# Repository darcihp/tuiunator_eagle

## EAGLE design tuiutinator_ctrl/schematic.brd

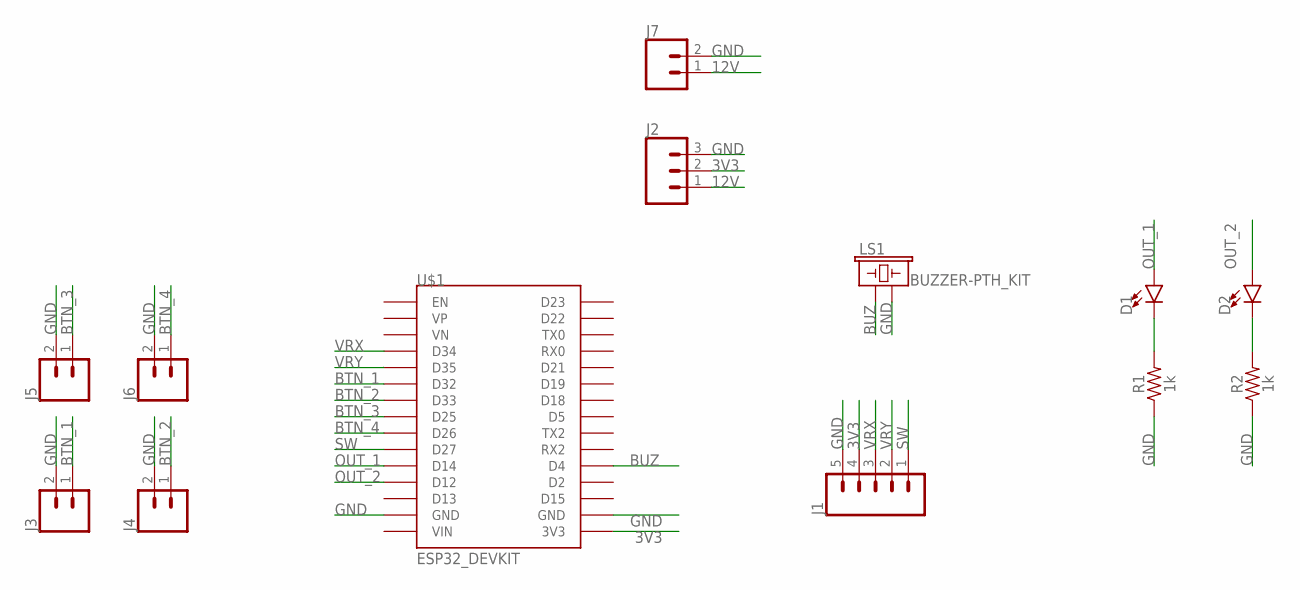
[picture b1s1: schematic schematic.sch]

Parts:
D1, D2: LED5MM; LED_5MM
J1: CONN_05LOCK; 1X05_LOCK
J2: CONN_03SCREW; SCREWTERMINAL-3.5MM-3
J3, J4, J5, J6: CONN_02; 1X02
J7: CONN_02LOCK; 1X02_LOCK
LS1: BUZZER-PTH_KIT; BUZZER-12MM-KIT
R1, R2: 1k; AXIAL-0.3
U$1: ESP32_DEVKIT

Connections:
3V3: J1.4, J2.2, U$1.3V3
12V: J2.1, J7.1
BTN_1: J3.1, U$1.D32
BTN_2: J4.1, U$1.D33
BTN_3: J5.1, U$1.D25
BTN_4: J6.1, U$1.D26
BUZ: LS1.+ (1), U$1.D4
GND: J1.5, J2.3, J3.2, J4.2, J5.2, J6.2, J7.2, LS1.- (2), R1.P$1 (1), R2.P$1 (1), U$1.GND@1 (GND), U$1.GND@2 (GND)
unnamed: D1.K (C), R1.P$2 (2)
unnamed: D2.K (C), R2.P$2 (2)
OUT_1: D1.A, U$1.D14
OUT_2: D2.A, U$1.D12
SW: J1.1, U$1.D27
VRX: J1.3, U$1.D34
VRY: J1.2, U$1.D35

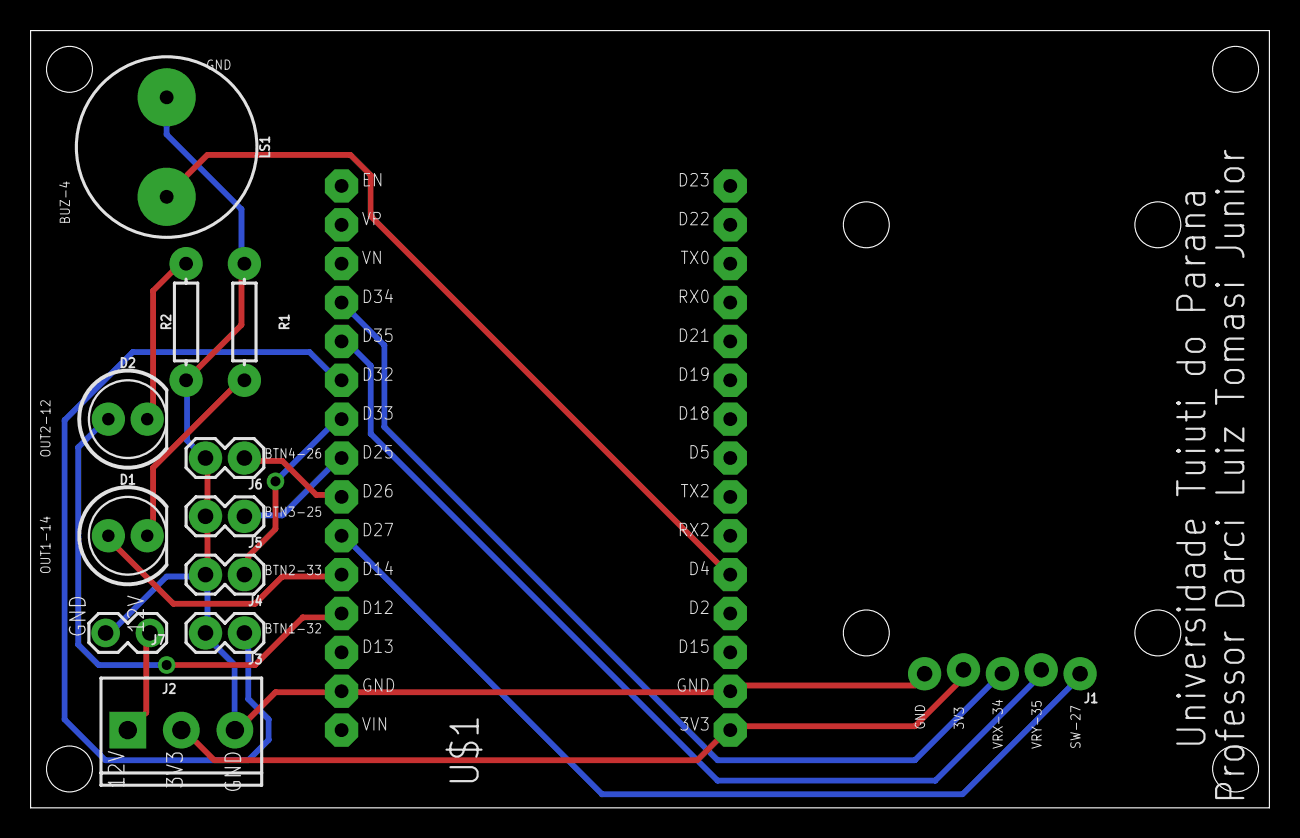
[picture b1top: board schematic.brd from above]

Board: 2 copper layers, 81.0 x 50.8 mm, 13 parts (0 on the bottom side), 15 nets.

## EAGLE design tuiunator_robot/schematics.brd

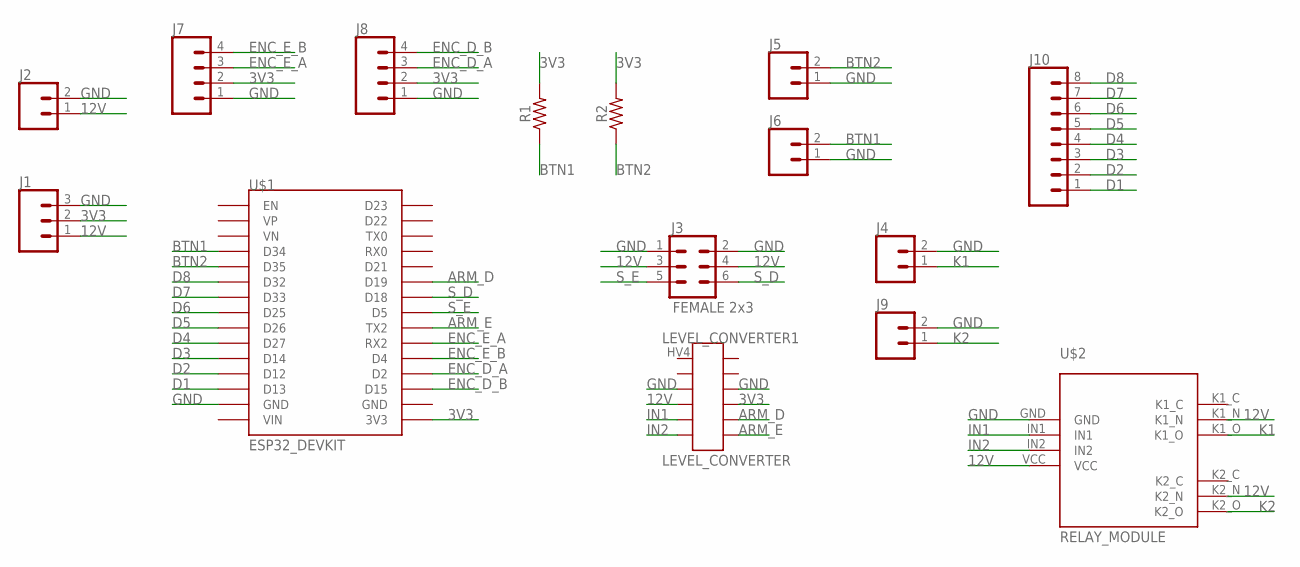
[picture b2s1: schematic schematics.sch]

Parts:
J1: CONN_03LOCK; 1X03_LOCK
J2, J5, J6: CONN_02LOCK; 1X02_LOCK
J3: FEMALE 2x3; 2X3
J4, J9: CONN_02PTH4; 1X02_XTRA_BIG
J7, J8: CONN_04LOCK; 1X04_LOCK
J10: CONN_08LOCK; 1X08_LOCK
LEVEL_CONVERTER1: LEVEL_CONVERTER
R1, R2: AXIAL-0.3
U$1: ESP32_DEVKIT
U$2: RELAY_MODULE

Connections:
3V3: J1.2, J7.2, J8.2, LEVEL_CONVERTER1.LV, R1.P$2 (2), R2.P$2 (2), U$1.3V3
12V: J1.1, J2.1, J3.3, J3.4, LEVEL_CONVERTER1.HV, U$2.K1_N, U$2.K2_N, U$2.VCC
ARM_D: LEVEL_CONVERTER1.LV2, U$1.D19
ARM_E: LEVEL_CONVERTER1.LV1, U$1.TX2
BTN1: J6.2, R1.P$1 (1), U$1.D34
BTN2: J5.2, R2.P$1 (1), U$1.D35
D1: J10.1, U$1.D13
D2: J10.2, U$1.D12
D3: J10.3, U$1.D14
D4: J10.4, U$1.D27
D5: J10.5, U$1.D26
D6: J10.6, U$1.D25
D7: J10.7, U$1.D33
D8: J10.8, U$1.D32
ENC_D_A: J8.3, U$1.D2
ENC_D_B: J8.4, U$1.D15
ENC_E_A: J7.3, U$1.RX2
ENC_E_B: J7.4, U$1.D4
GND: J1.3, J2.2, J3.1, J3.2, J4.2, J5.1, J6.1, J7.1, J8.1, J9.2, LEVEL_CONVERTER1.GNDH, LEVEL_CONVERTER1.GNDL, U$1.GND@1 (GND), U$2.GND
IN1: LEVEL_CONVERTER1.HV2, U$2.IN1
IN2: LEVEL_CONVERTER1.HV1, U$2.IN2
K1: J4.1, U$2.K1_O
K2: J9.1, U$2.K2_O
S_D: J3.6, U$1.D18
S_E: J3.5, U$1.D5

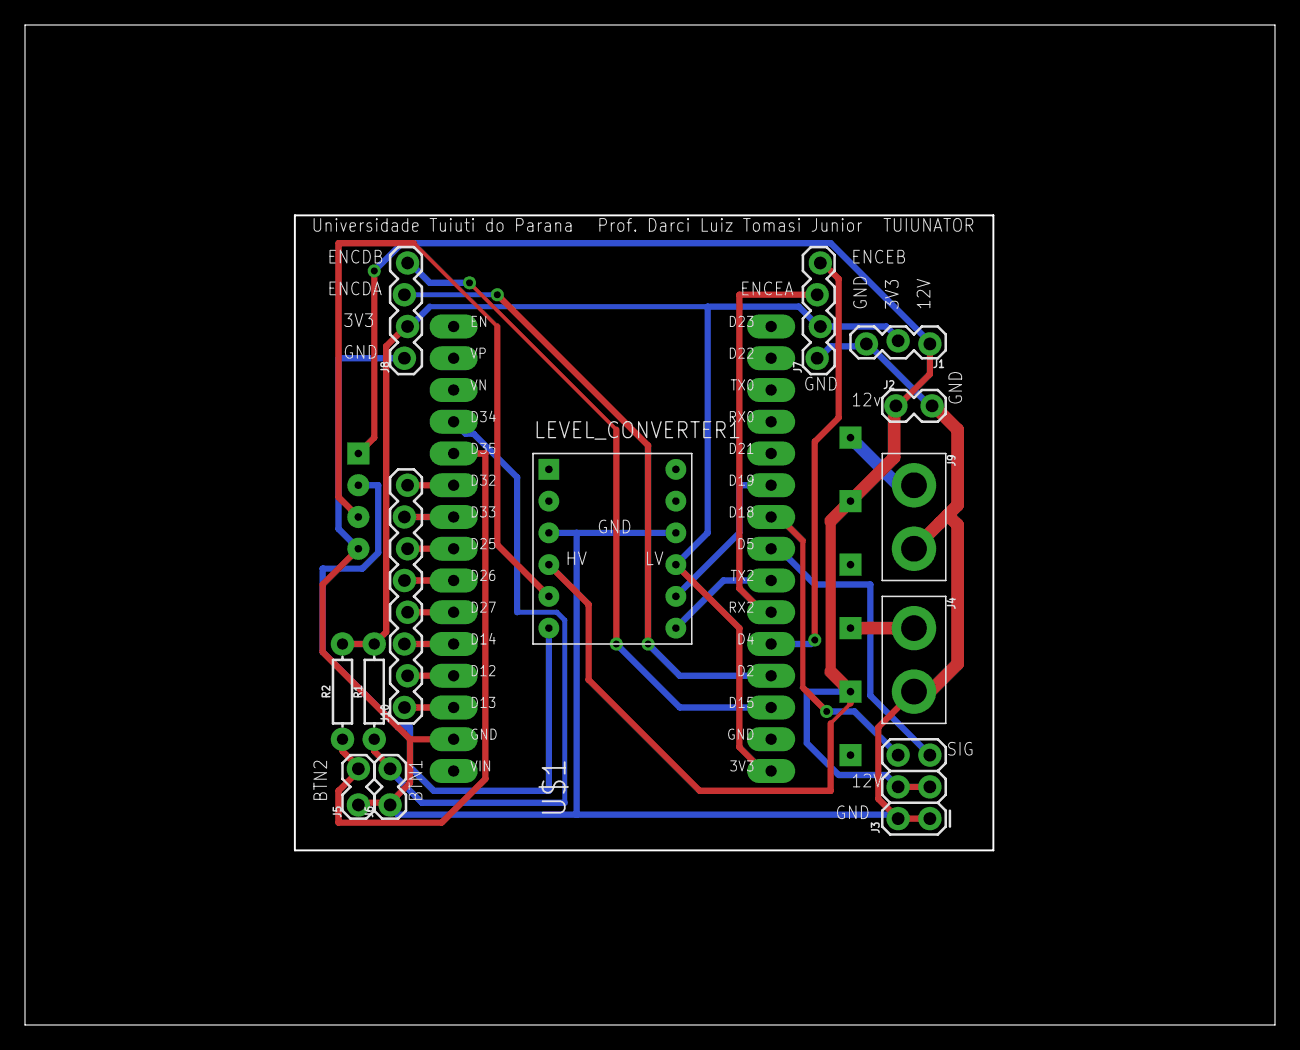
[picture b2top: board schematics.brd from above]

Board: 2 copper layers, 99.8 x 79.8 mm, 15 parts (1 on the bottom side), 25 nets.

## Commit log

2025-05-29 Versão da placa do robô
2025-05-30 Primeira versão do controle
    Somente esquemático finalizado
2025-06-27 Versão com controle pronto enviado para JLC

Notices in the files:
parts and their libraries:
SparkFun-Connectors: Licensing: Creative Commons ShareAlike 4.0 International - https://creativecommons.org/licenses/by-sa/4.0
